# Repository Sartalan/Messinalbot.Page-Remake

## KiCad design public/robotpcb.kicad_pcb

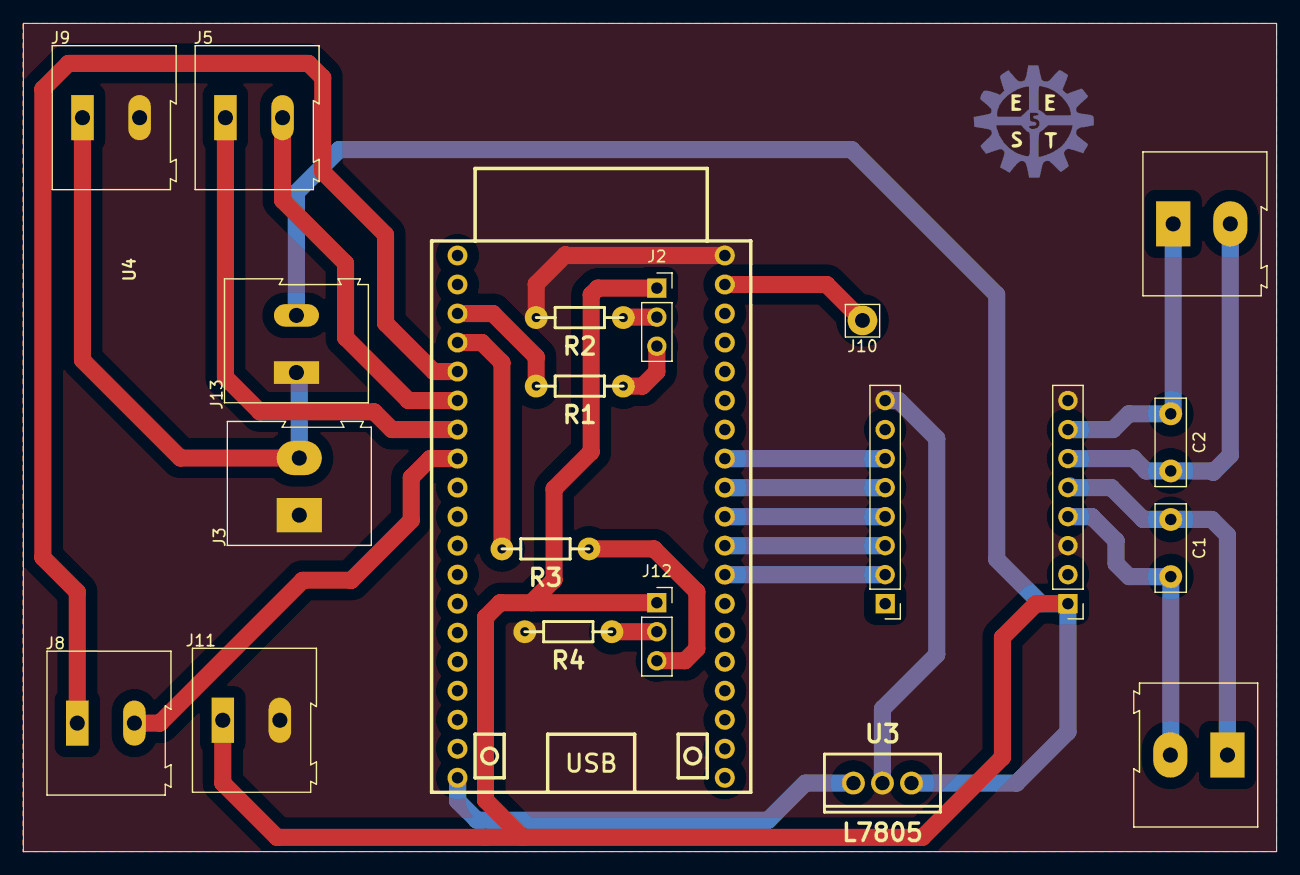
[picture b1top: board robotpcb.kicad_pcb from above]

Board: 2 copper layers, 109.7 x 72.5 mm, 21 parts (0 on the bottom side), 23 nets.

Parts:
C1, C2: C; C_Disc_D7.5mm_W2.5mm_P5.00mm
J1: Motor1; TerminalBlock_Altech_AK300-2_P5.00mm
J2, J12: Screw_Terminal_01x03; PinSocket_1x03_P2.54mm_Vertical
J3, J5, J8, J9, J11: BateriadeNotebook; TerminalBlock_Altech_AK300-2_P5.00mm
J4, J13: Motor2; TerminalBlock_Altech_AK300-2_P5.00mm
J6: DRV8833_O; PinHeader_1x08_P2.54mm_Vertical
J7: DRV883_I; PinHeader_1x08_P2.54mm_Vertical
J10: Screw_Terminal_01x01; Pin_D1.3mm_L11.3mm_W2.8mm_Flat
R1, R2, R3, R4: R; RES0.3
U3: L7805; TO-220
U4: ESP32_DEVKITC

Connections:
/5v: U3.3 (OUT), U4.19 (5V)
/IN UL: J8.1, U4.5 (IO34)
/IN UL 2: J5.2, U4.6 (IO35)
/IN inf: R1.2, U4.3 (SVP)
/IN inf 2: R3.2, U4.4 (SVN)
/MA1: J7.3, U4.28 (IO17)
/MA2: J7.2, U4.27 (IO16)
/MB1: J7.5, U4.30 (IO18)
/MB2: J7.6, U4.31 (IO19)
/MO1: C1.2, J4.2, J6.4
/MO2: C1.1, J4.1, J6.5
/MO3: C2.2, J1.2, J6.6
/MO4: C2.1, J1.1, J6.7
/OUT UL: J5.1, U4.7 (IO32)
/OUT UL 2: J8.2, U4.8 (IO33)
/STBY: J7.4, U4.29 (IO5)
/Vcc: J2.1, J3.2, J6.1, J9.1, J11.1, J12.1, J13.2, U3.1 (IN)
/swich est: J10.1, U4.37 (IO23)
GND: J3.1, J6.3, J6.8, J7.8, J9.2, J11.2, J13.1, R2.2, R4.2, U3.2 (GND), U4.38 (GND)
unnamed: J2.2, R2.1
unnamed: J2.3, R1.1
unnamed: J12.2, R4.1
unnamed: J12.3, R3.1

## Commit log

2024-06-30 [Comienzo del Proyecto | Estructura | v0.1]
2024-06-30 Añadido de 'List' | v0.2
2024-07-03 Nav Data && Map Finished | v0.3
2024-07-03 Structure Refactoring | v0.4
2024-07-04 List Style Improvement | v0.5
2024-07-07 Home Feature | v0.6
2024-07-07 PCB Feature | v0.7
2024-07-08 PCB-Screen: List Improvement | v0.8
2024-07-08 PCB|Home-Screen: Mobile Responsive Improvement | v0.9
2025-08-27 Code | Code-Screen: Added | v1.0
